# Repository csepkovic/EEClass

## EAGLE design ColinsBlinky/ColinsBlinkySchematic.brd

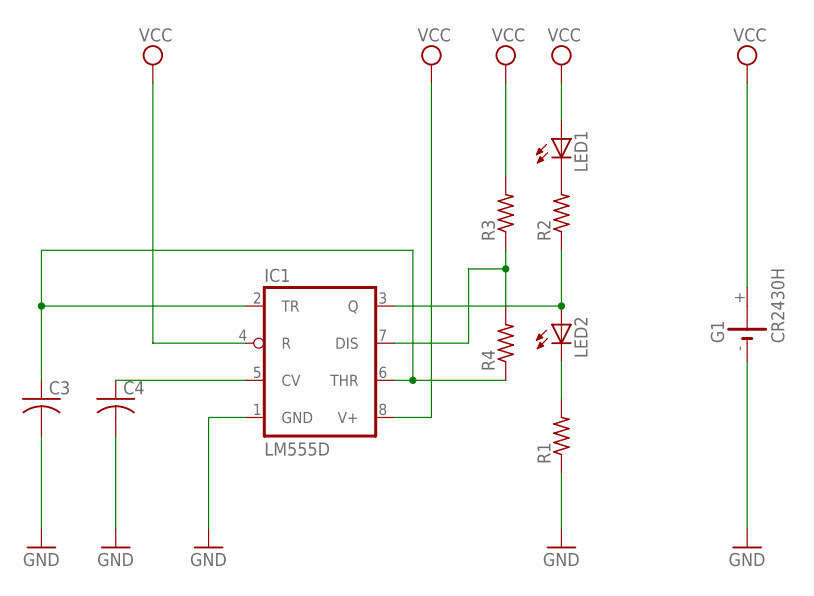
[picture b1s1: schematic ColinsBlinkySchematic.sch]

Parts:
C3, C4: C-USC0805; C0805
G1: CR2430H
IC1: LM555D; SO08
LED1, LED2: LED5MM
R1, R2, R3, R4: R-US_R0805; R0805

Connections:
GND: C3.2, C4.2, G1.-, IC1.1 (GND), R1.1
unnamed: IC1.3 (Q), LED2.A, R2.1
unnamed: LED2.K (C), R1.2
unnamed: IC1.7 (DIS), R3.1, R4.2
unnamed: C4.1, IC1.5 (CV)
unnamed: C3.1, IC1.2 (TR), IC1.6 (THR), R4.1
unnamed: LED1.K (C), R2.2
VCC: G1.+, IC1.4 (R), IC1.8 (V+), LED1.A, R3.2

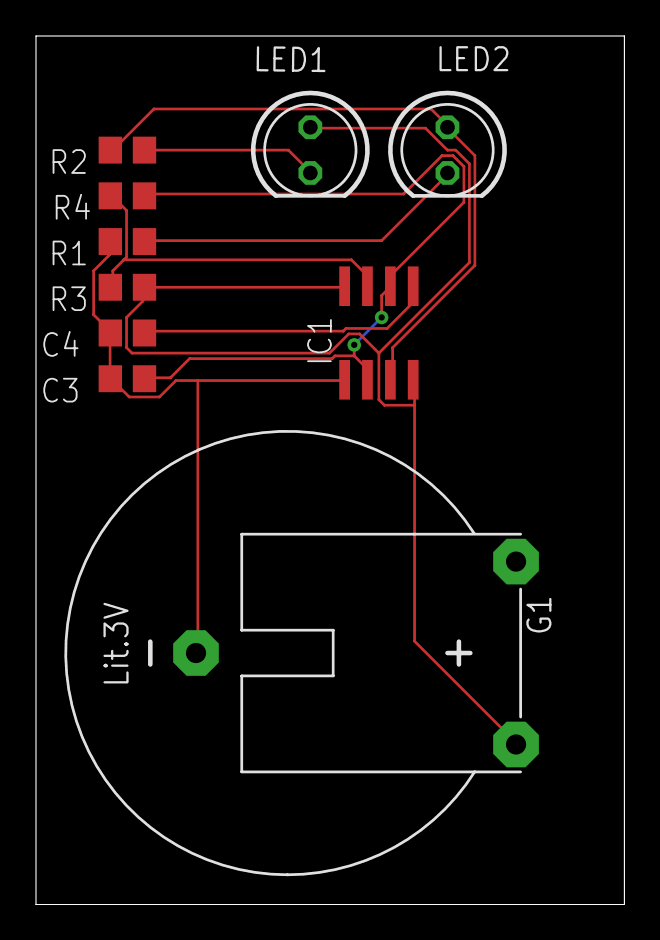
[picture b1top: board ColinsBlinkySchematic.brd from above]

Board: 2 copper layers, 32.7 x 48.2 mm, 10 parts (0 on the bottom side), 8 nets.

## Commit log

2018-05-12 Week 1 Day 6
2018-05-17 Week 2 Day 4
